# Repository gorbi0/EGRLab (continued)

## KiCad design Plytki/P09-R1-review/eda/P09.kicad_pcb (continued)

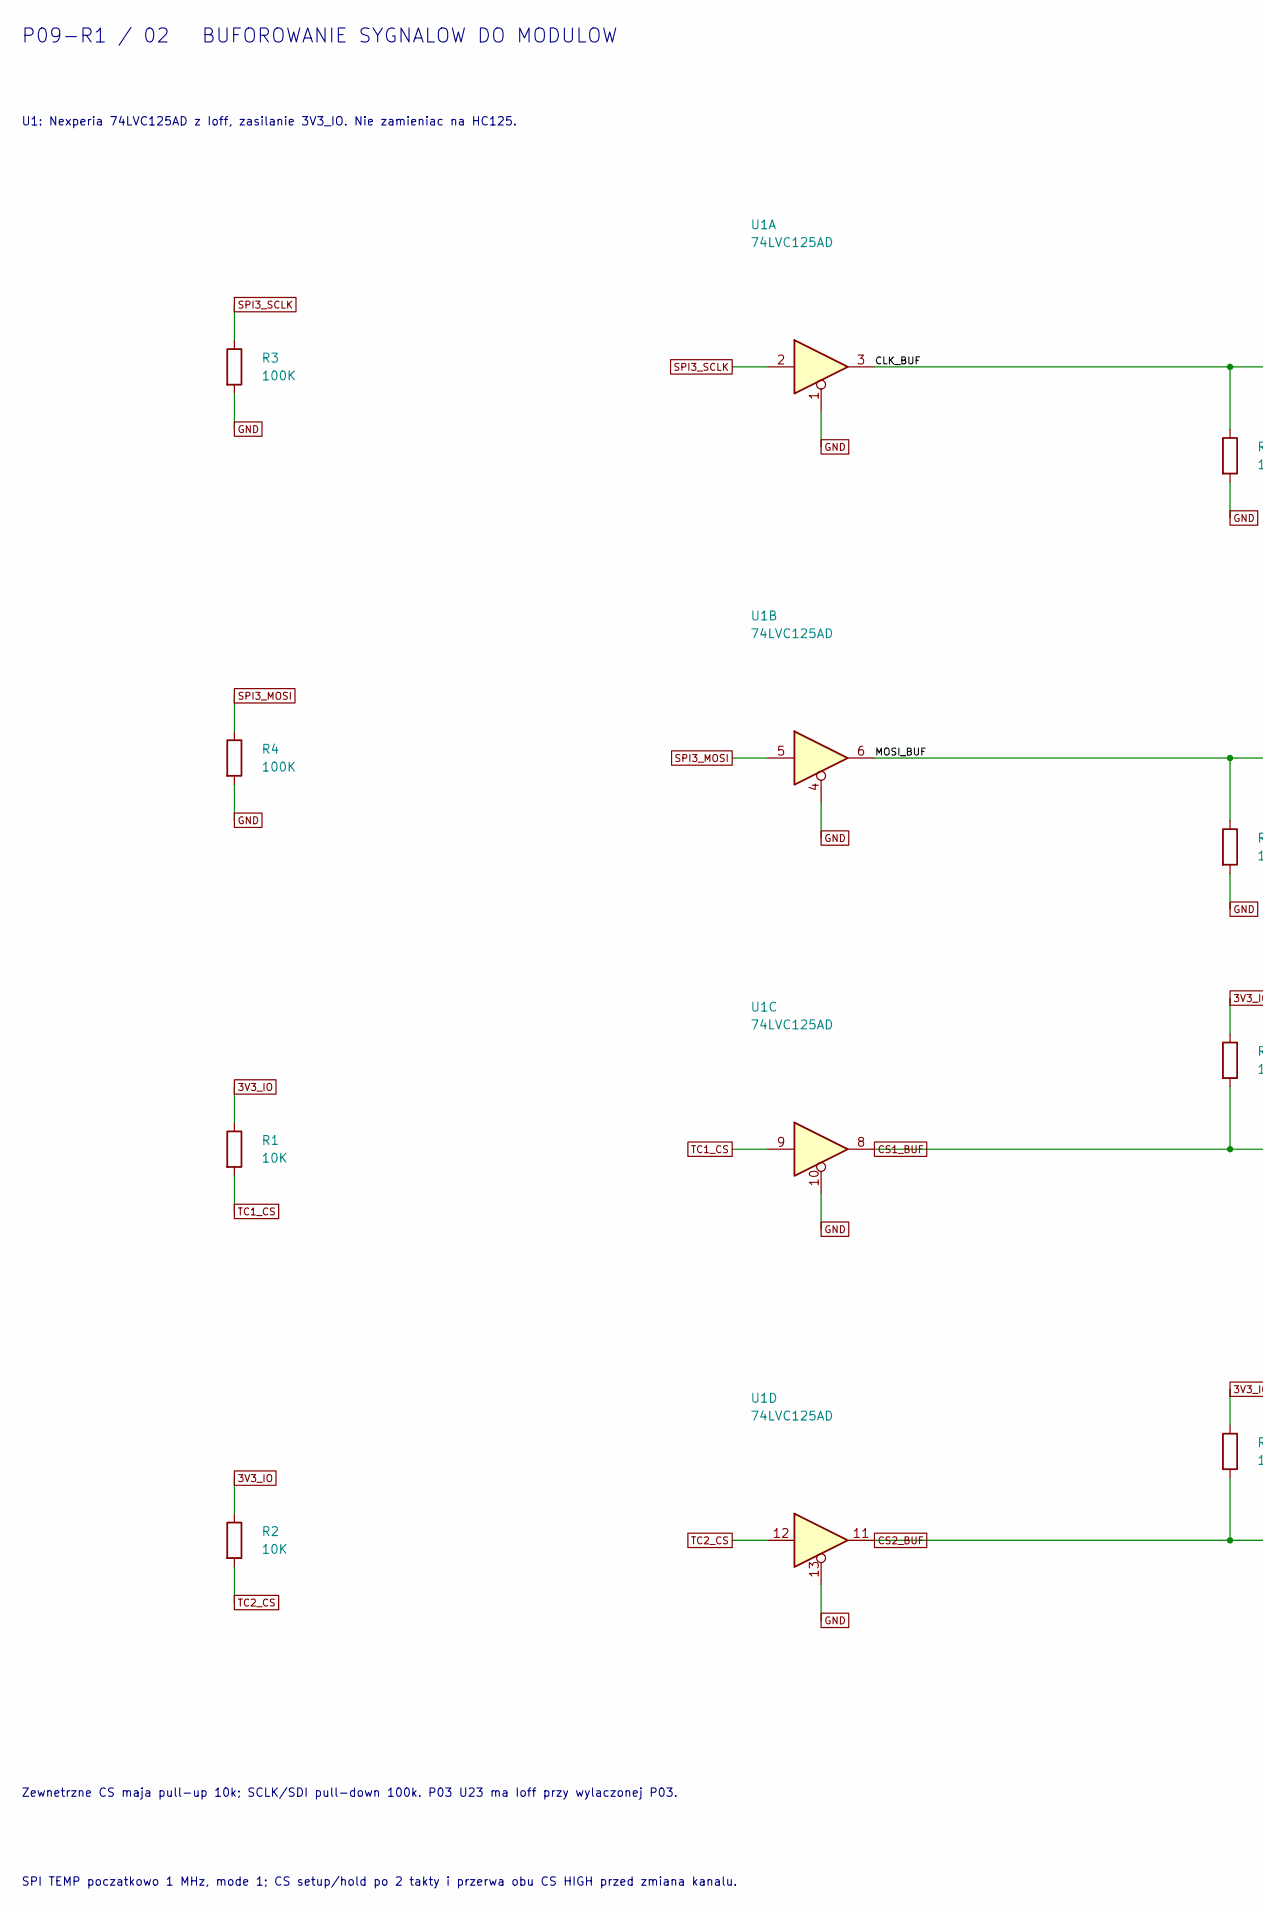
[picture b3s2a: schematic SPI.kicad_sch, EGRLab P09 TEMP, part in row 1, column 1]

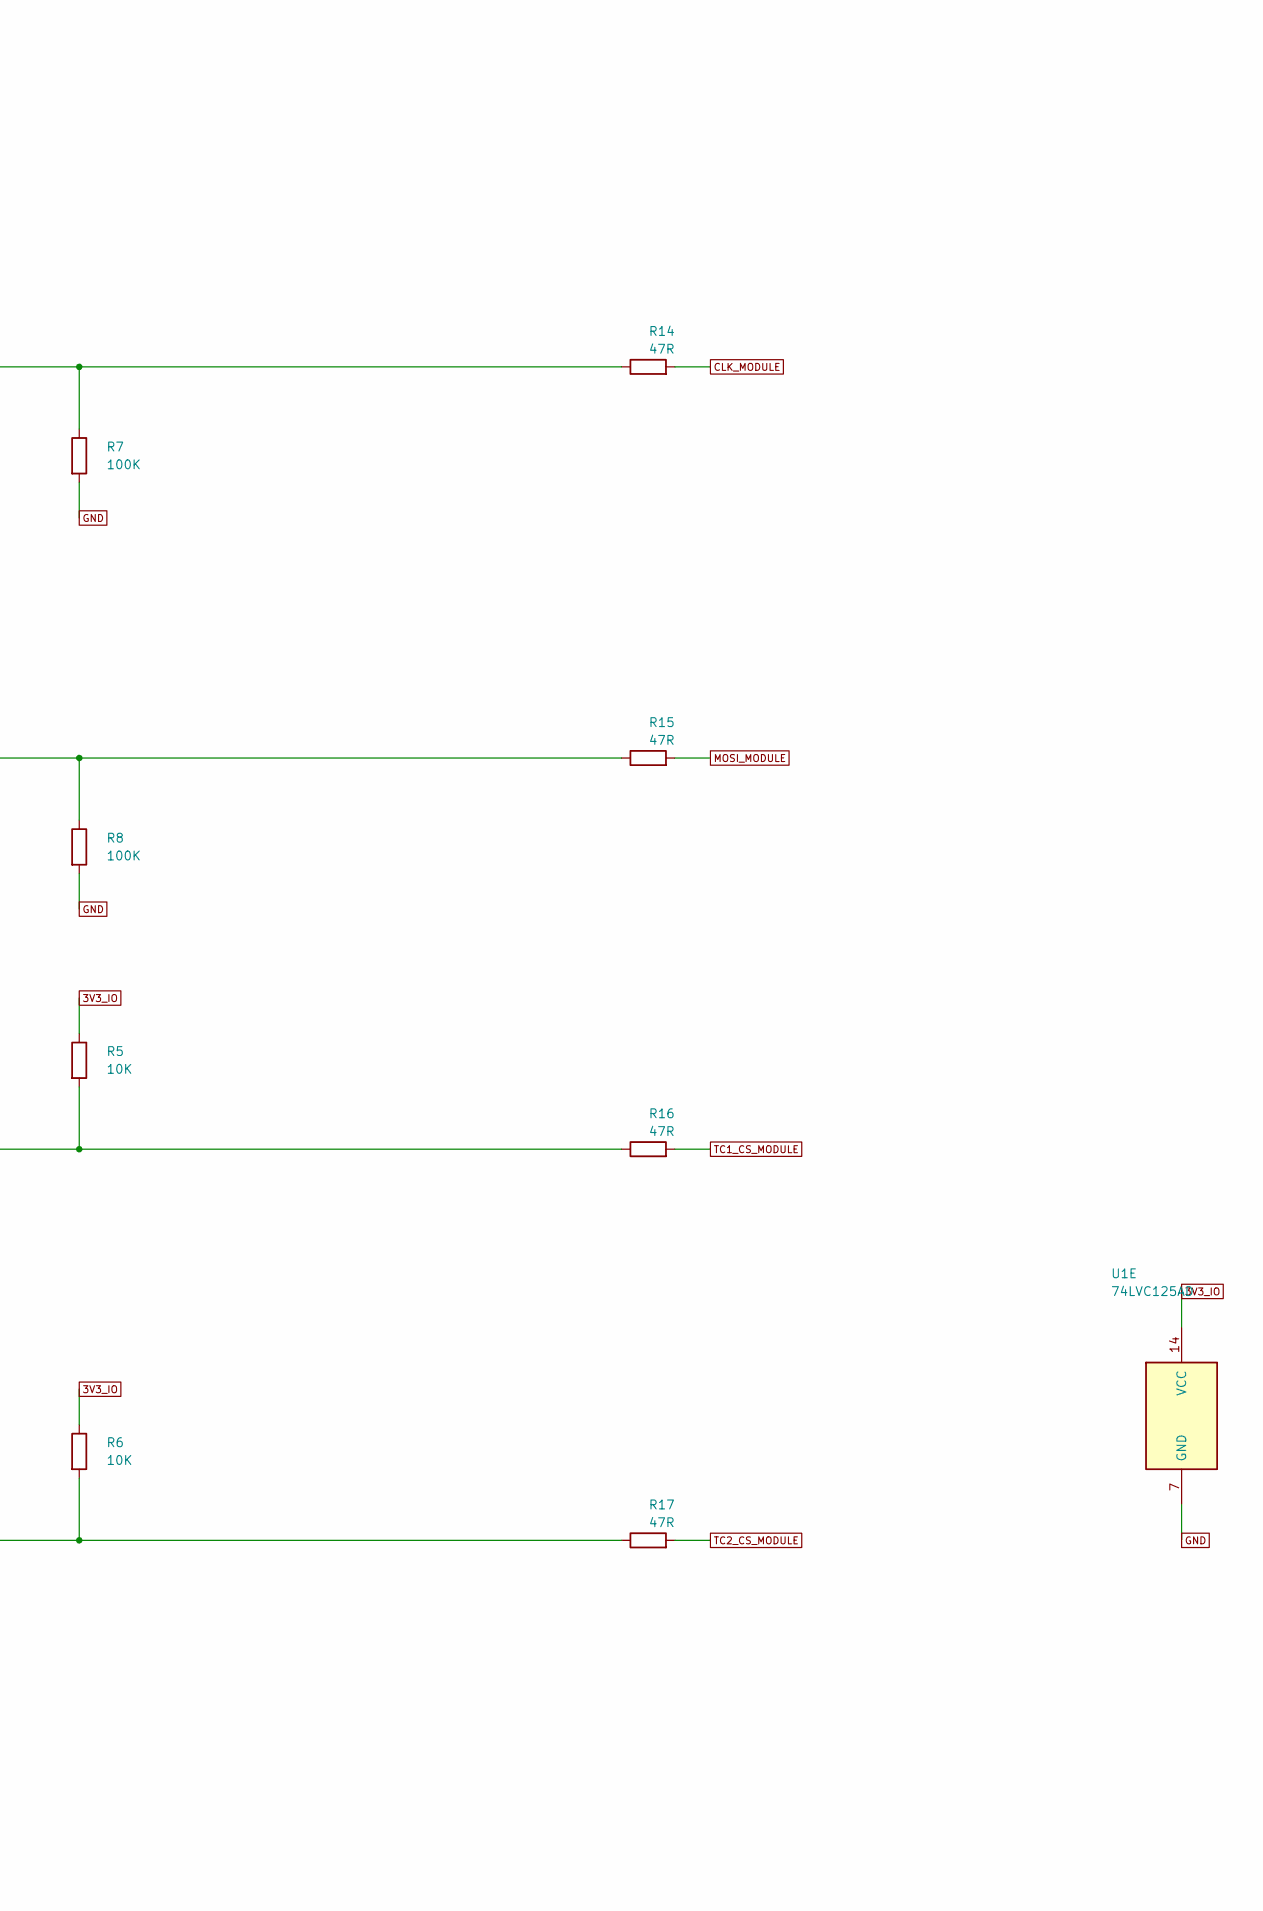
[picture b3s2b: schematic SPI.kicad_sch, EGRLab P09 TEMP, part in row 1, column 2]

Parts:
R1, R2, R5, R6: 10K; R_Axial_DIN0207_L6.3mm_D2.5mm_P10.16mm_Horizontal; MPN Metal film 10K 1% 0.25W
R3, R4, R7, R8: 100K; R_Axial_DIN0207_L6.3mm_D2.5mm_P10.16mm_Horizontal; MPN Metal film 100K 1% 0.25W
R14, R15, R16, R17: 47R; R_Axial_DIN0207_L6.3mm_D2.5mm_P10.16mm_Horizontal; MPN Metal film 47R 1% 0.25W
U1: 74LVC125AD; SOIC-14_3.9x8.7mm_P1.27mm; MPN 74LVC125AD,118 Nexperia

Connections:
3V3_IO: R1.1, R2.1, R5.1, R6.1, U1.14 (VCC); also elsewhere on the board
/SPI/CLK_BUF: R7.1, R14.1, U1.3
/SPI/MOSI_BUF: R8.1, R15.1, U1.6
CLK_MODULE: R14.2; also elsewhere on the board
CS1_BUF: R5.2, R16.1, U1.8; also elsewhere on the board
CS2_BUF: R6.2, R17.1, U1.11; also elsewhere on the board
GND: R3.2, R4.2, R7.2, R8.2, U1.1, U1.4, U1.7 (GND), U1.10, U1.13; also elsewhere on the board
MOSI_MODULE: R15.2; also elsewhere on the board
SPI3_MOSI: R4.1, U1.5; also elsewhere on the board
SPI3_SCLK: R3.1, U1.2; also elsewhere on the board
TC1_CS: R1.2, U1.9; also elsewhere on the board
TC1_CS_MODULE: R16.2; also elsewhere on the board
TC2_CS: R2.2, U1.12; also elsewhere on the board
TC2_CS_MODULE: R17.2; also elsewhere on the board

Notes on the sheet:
U1: Nexperia 74LVC125AD z Ioff, zasilanie 3V3_IO. Nie zamieniac na HC125.
Zewnetrzne CS maja pull-up 10k; SCLK/SDI pull-down 100k. P03 U23 ma Ioff przy wylaczonej P03.
SPI TEMP poczatkowo 1 MHz, mode 1; CS setup/hold po 2 takty i przerwa obu CS HIGH przed zmiana kanalu.
P09-R1 / 02 BUFOROWANIE SYGNALOW DO MODULOW

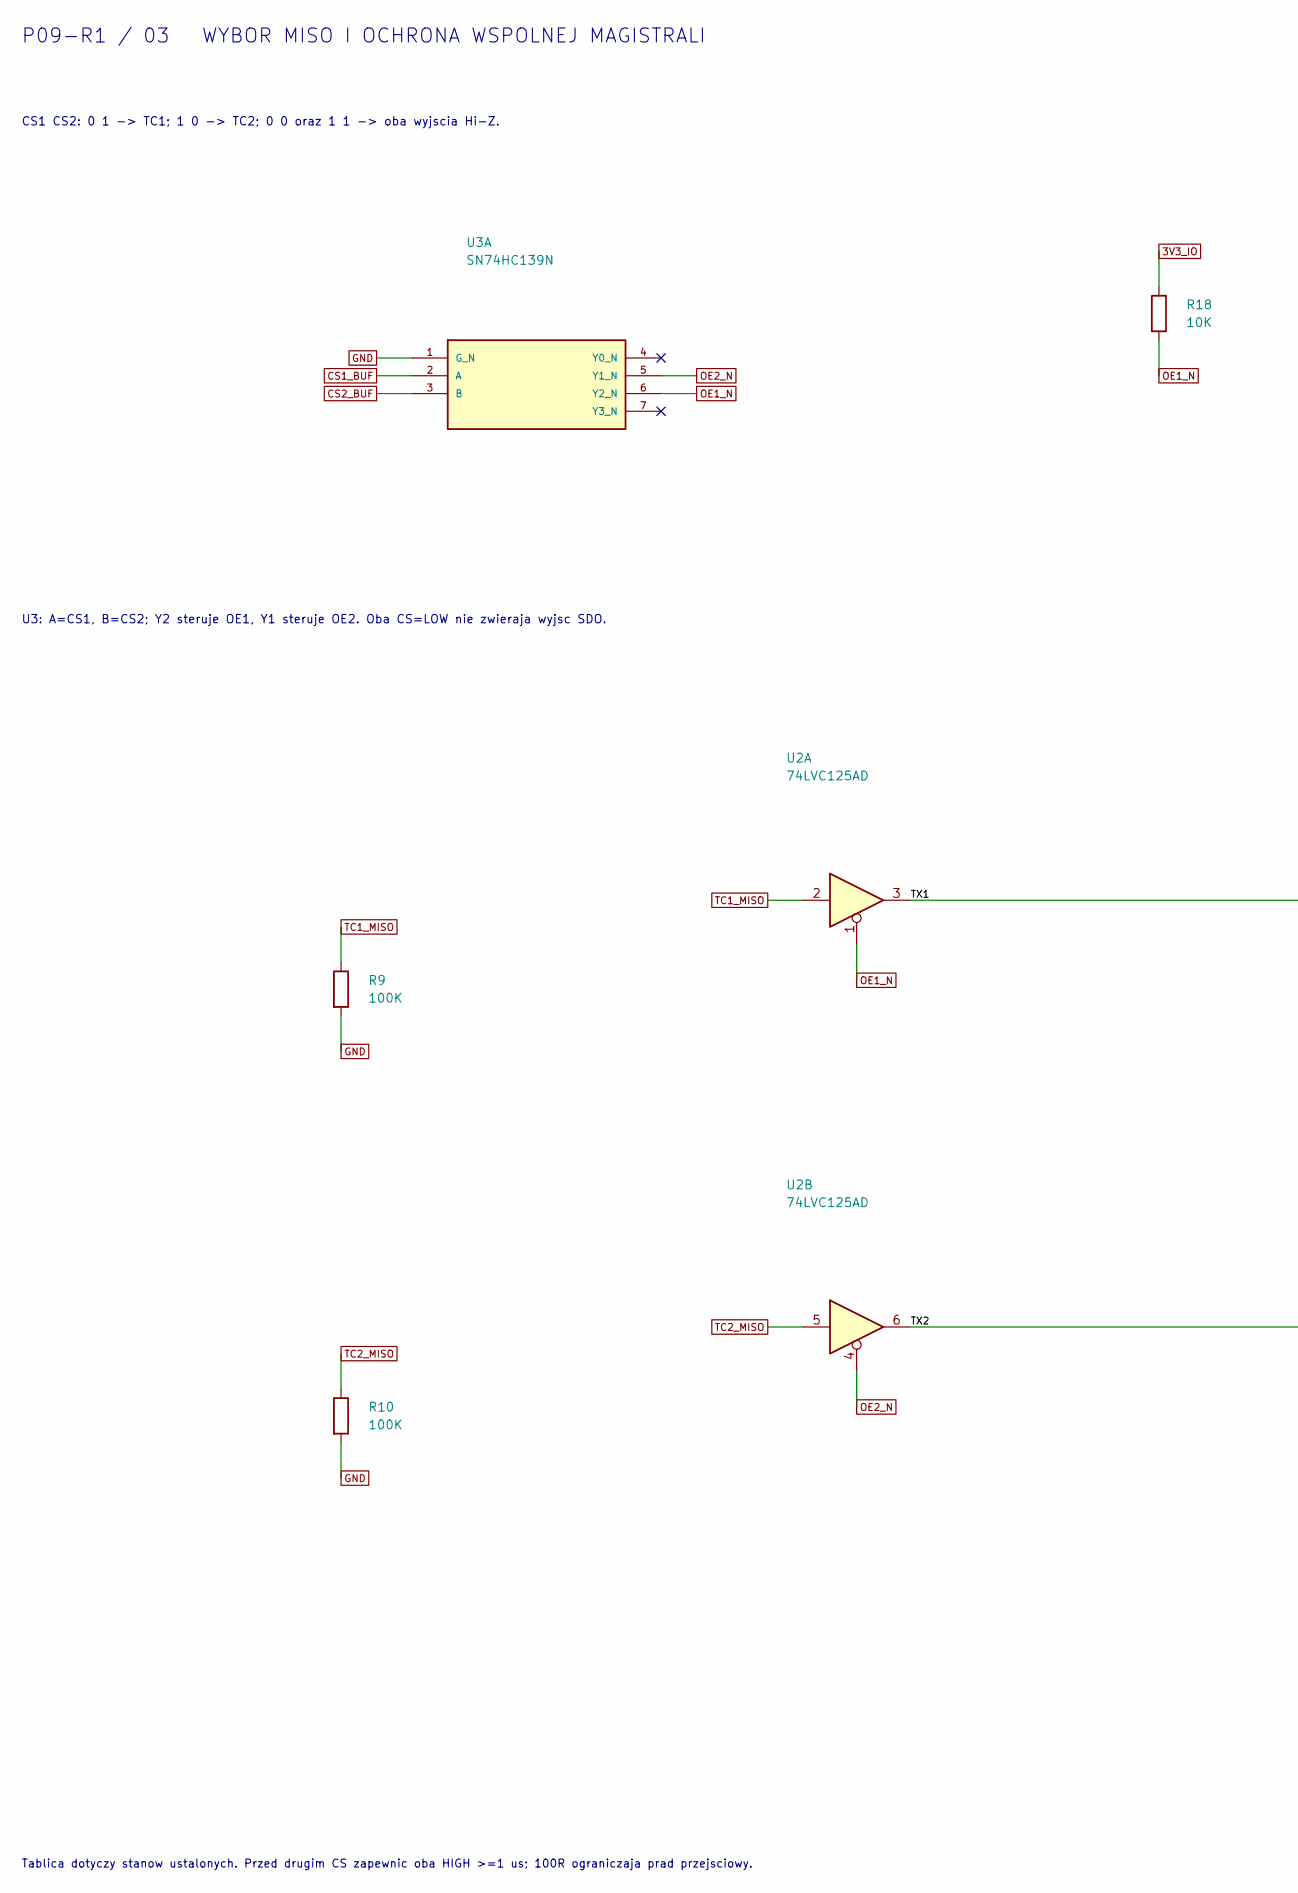
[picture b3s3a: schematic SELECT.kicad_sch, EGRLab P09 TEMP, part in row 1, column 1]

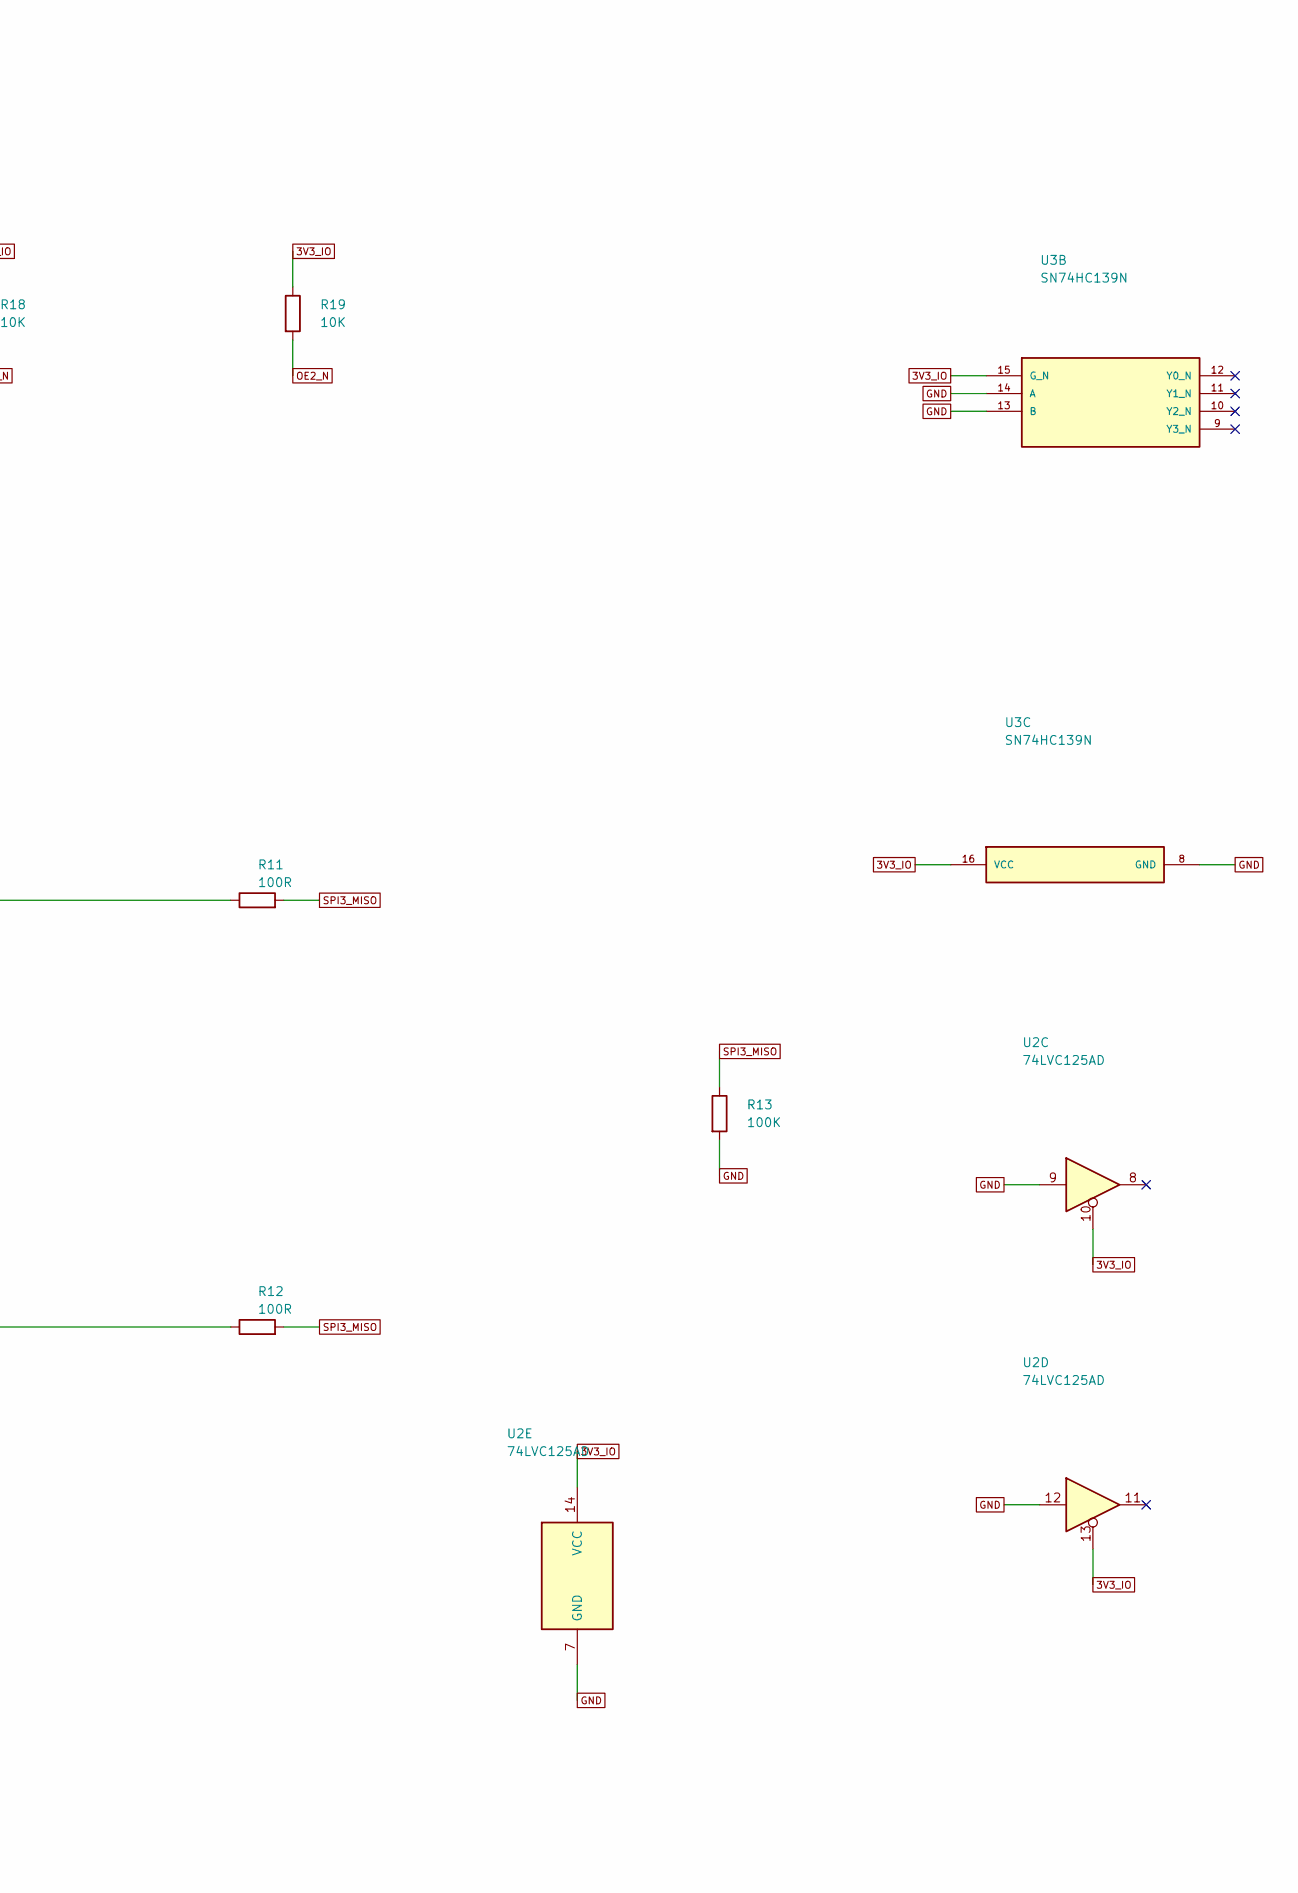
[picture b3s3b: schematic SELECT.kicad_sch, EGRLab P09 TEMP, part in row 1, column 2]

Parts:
R9, R10, R13: 100K; R_Axial_DIN0207_L6.3mm_D2.5mm_P10.16mm_Horizontal; MPN Metal film 100K 1% 0.25W
R11, R12: 100R; R_Axial_DIN0207_L6.3mm_D2.5mm_P10.16mm_Horizontal; MPN Metal film 100R 1% 0.25W
R18, R19: 10K; R_Axial_DIN0207_L6.3mm_D2.5mm_P10.16mm_Horizontal; MPN Metal film 10K 1% 0.25W
U2: 74LVC125AD; SOIC-14_3.9x8.7mm_P1.27mm; MPN 74LVC125AD,118 Nexperia
U3: SN74HC139N; DIP-16_W7.62mm; MPN SN74HC139N

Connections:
3V3_IO: R18.1, R19.1, U2.10, U2.13, U2.14 (VCC), U3.15 (G_N), U3.16 (VCC); also elsewhere on the board
/SELECT/TX1: R11.1, U2.3
/SELECT/TX2: R12.1, U2.6
CS1_BUF: U3.2 (A); also elsewhere on the board
CS2_BUF: U3.3 (B); also elsewhere on the board
GND: R9.2, R10.2, R13.2, U2.7 (GND), U2.9, U2.12, U3.1 (G_N), U3.8 (GND), U3.13 (B), U3.14 (A); also elsewhere on the board
OE1_N: R18.2, U2.1, U3.6 (Y2_N); also elsewhere on the board
OE2_N: R19.2, U2.4, U3.5 (Y1_N); also elsewhere on the board
SPI3_MISO: R11.2, R12.2, R13.1; also elsewhere on the board
TC1_MISO: R9.1, U2.2; also elsewhere on the board
TC2_MISO: R10.1, U2.5; also elsewhere on the board

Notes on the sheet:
CS1 CS2: 0 1 -> TC1; 1 0 -> TC2; 0 0 oraz 1 1 -> oba wyjscia Hi-Z.
U3: A=CS1, B=CS2; Y2 steruje OE1, Y1 steruje OE2. Oba CS=LOW nie zwieraja wyjsc SDO.
Tablica dotyczy stanow ustalonych. Przed drugim CS zapewnic oba HIGH >=1 us; 100R ograniczaja prad przejsciowy.
P09-R1 / 03 WYBOR MISO I OCHRONA WSPOLNEJ MAGISTRALI

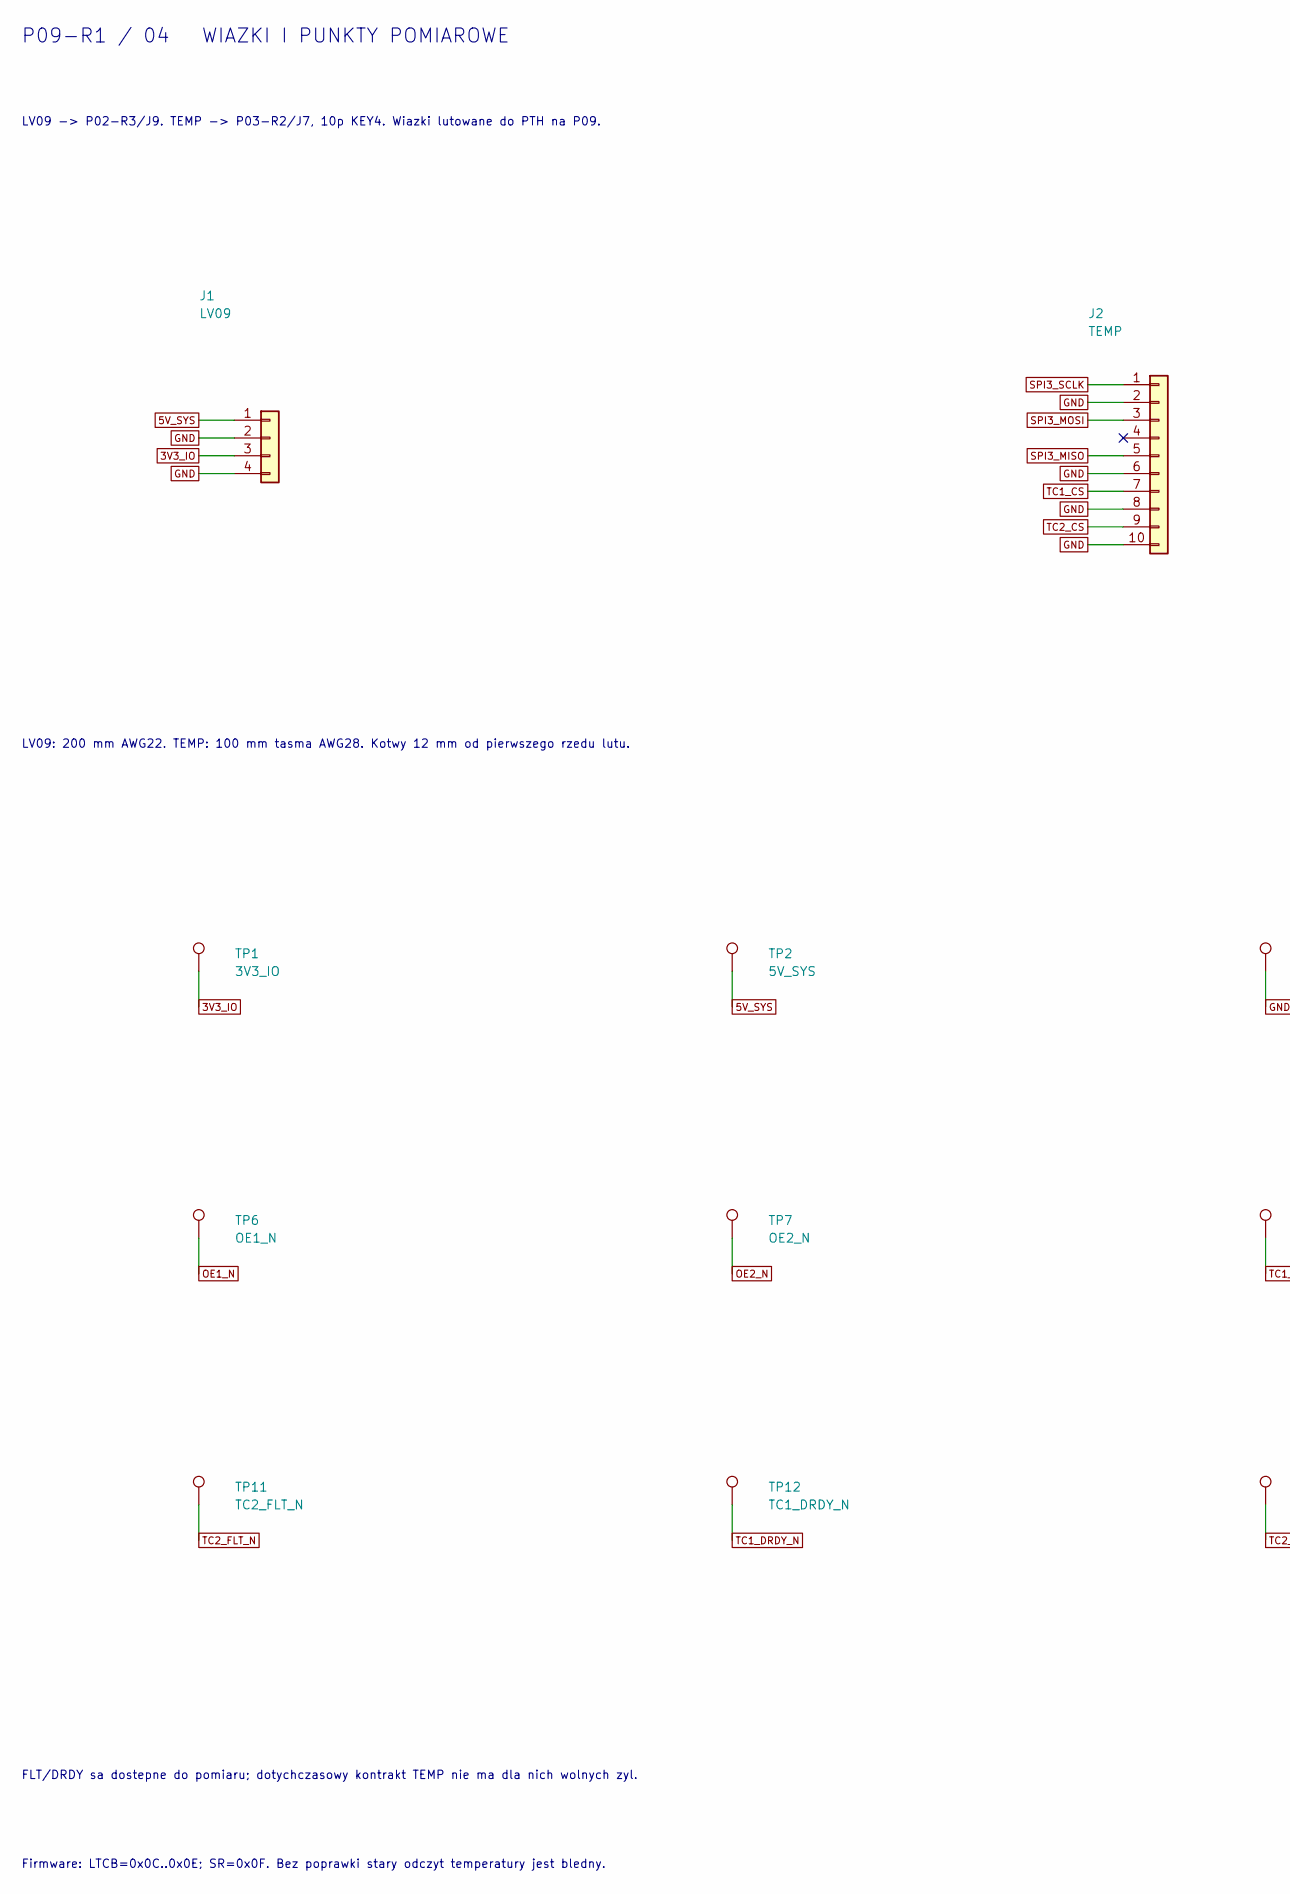
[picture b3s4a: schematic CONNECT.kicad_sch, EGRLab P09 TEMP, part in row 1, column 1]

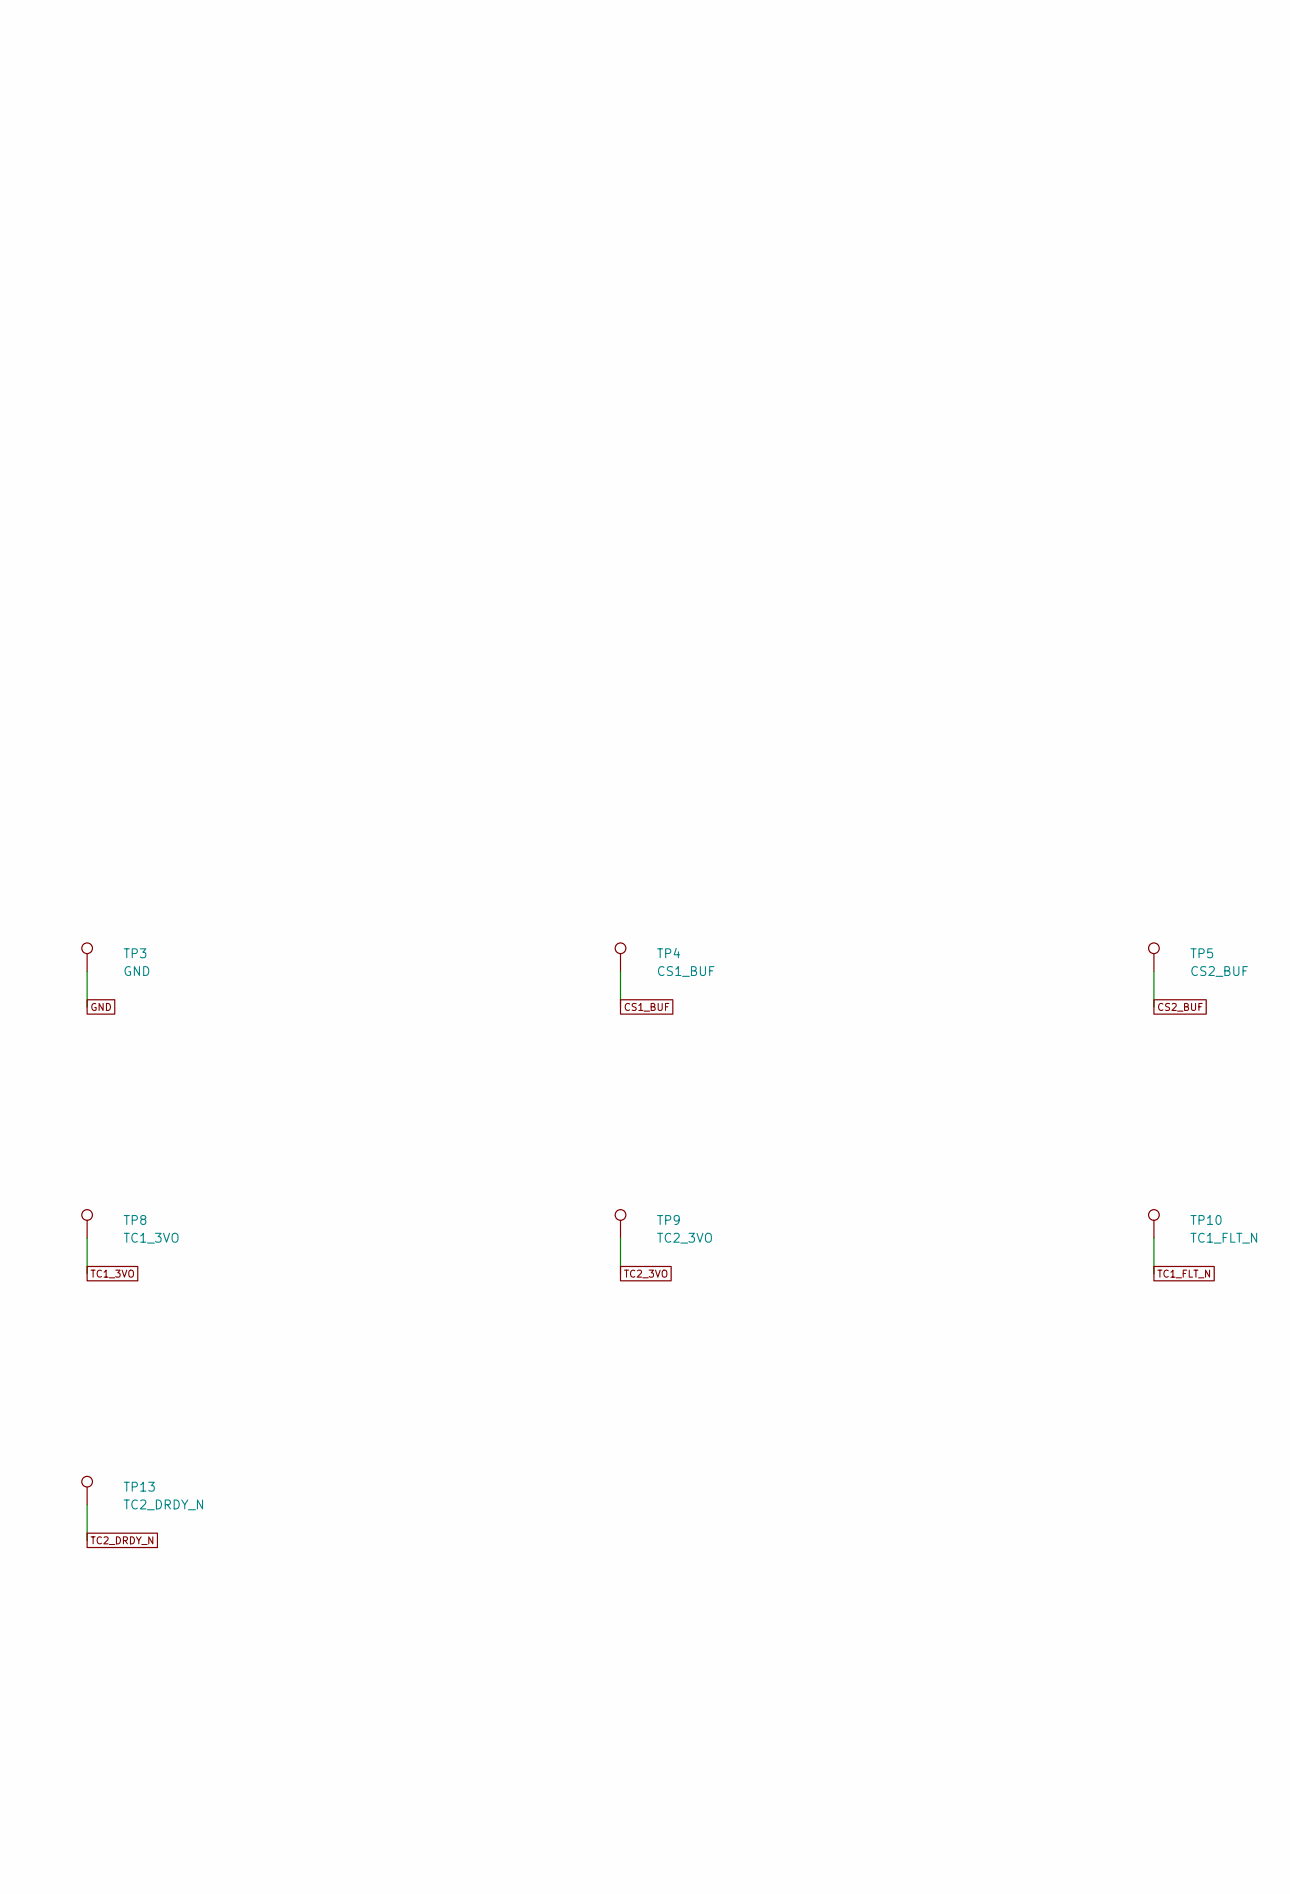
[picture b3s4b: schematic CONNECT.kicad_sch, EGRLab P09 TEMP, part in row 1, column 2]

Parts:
J1: LV09; PTH_LV09; MPN Soldered harness
J2: TEMP; PTH_TEMP; MPN Soldered harness
TP1: 3V3_IO; TestPad_1; MPN PCB test pad
TP2: 5V_SYS; TestPad_1; MPN PCB test pad
TP3: GND; TestPad_1; MPN PCB test pad
TP4: CS1_BUF; TestPad_1; MPN PCB test pad
TP5: CS2_BUF; TestPad_1; MPN PCB test pad
TP6: OE1_N; TestPad_1; MPN PCB test pad
TP7: OE2_N; TestPad_1; MPN PCB test pad
TP8: TC1_3VO; TestPad_1; MPN PCB test pad
TP9: TC2_3VO; TestPad_1; MPN PCB test pad
TP10: TC1_FLT_N; TestPad_1; MPN PCB test pad
TP11: TC2_FLT_N; TestPad_1; MPN PCB test pad
TP12: TC1_DRDY_N; TestPad_1; MPN PCB test pad
TP13: TC2_DRDY_N; TestPad_1; MPN PCB test pad

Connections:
3V3_IO: J1.3, TP1.1; also elsewhere on the board
5V_SYS: J1.1, TP2.1; also elsewhere on the board
CS1_BUF: TP4.1; also elsewhere on the board
CS2_BUF: TP5.1; also elsewhere on the board
GND: J1.2, J1.4, J2.2, J2.6, J2.8, J2.10, TP3.1; also elsewhere on the board
OE1_N: TP6.1; also elsewhere on the board
OE2_N: TP7.1; also elsewhere on the board
SPI3_MISO: J2.5; also elsewhere on the board
SPI3_MOSI: J2.3; also elsewhere on the board
SPI3_SCLK: J2.1; also elsewhere on the board
TC1_3VO: TP8.1; also elsewhere on the board
TC1_CS: J2.7; also elsewhere on the board
TC1_DRDY_N: TP12.1; also elsewhere on the board
TC1_FLT_N: TP10.1; also elsewhere on the board
TC2_3VO: TP9.1; also elsewhere on the board
TC2_CS: J2.9; also elsewhere on the board
TC2_DRDY_N: TP13.1; also elsewhere on the board
TC2_FLT_N: TP11.1; also elsewhere on the board

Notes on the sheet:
LV09 -> P02-R3/J9. TEMP -> P03-R2/J7, 10p KEY4. Wiazki lutowane do PTH na P09.
LV09: 200 mm AWG22. TEMP: 100 mm tasma AWG28. Kotwy 12 mm od pierwszego rzedu lutu.
FLT/DRDY sa dostepne do pomiaru; dotychczasowy kontrakt TEMP nie ma dla nich wolnych zyl.
Firmware: LTCB=0x0C..0x0E; SR=0x0F. Bez poprawki stary odczyt temperatury jest bledny.
P09-R1 / 04 WIAZKI I PUNKTY POMIAROWE

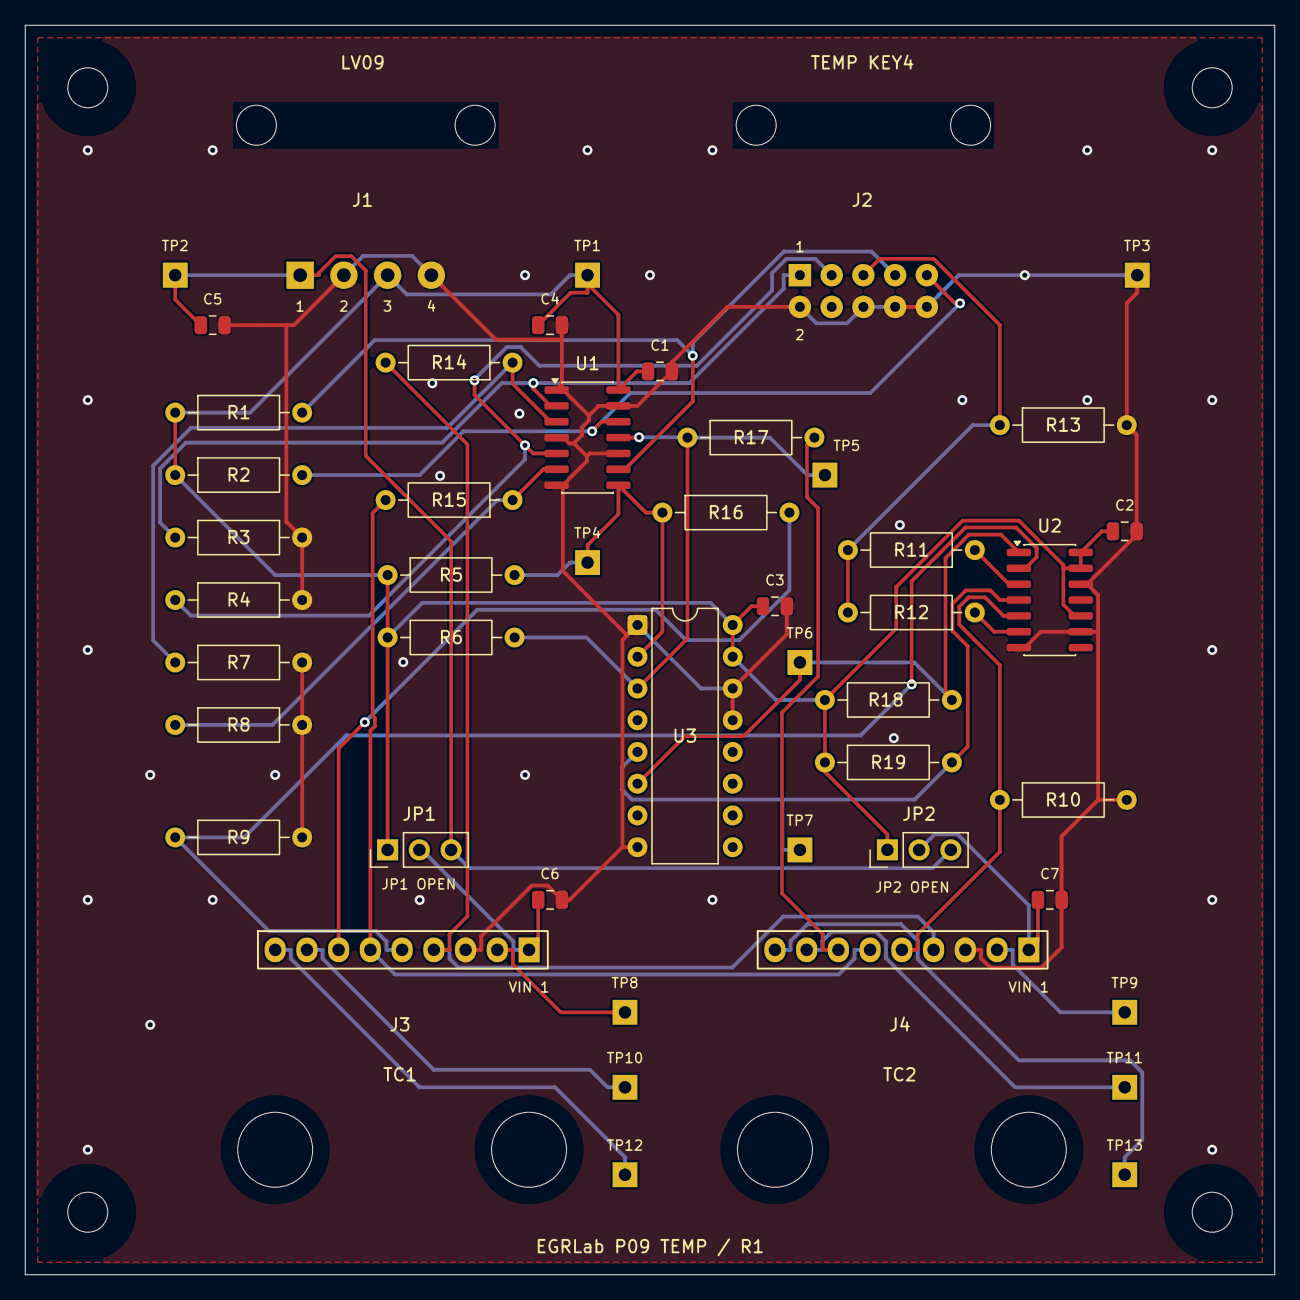
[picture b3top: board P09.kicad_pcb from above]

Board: 2 copper layers, 100.0 x 100.0 mm, 52 parts (0 on the bottom side), 30 nets.

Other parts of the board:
H1, H2, H3, H4: M3 NPTH
